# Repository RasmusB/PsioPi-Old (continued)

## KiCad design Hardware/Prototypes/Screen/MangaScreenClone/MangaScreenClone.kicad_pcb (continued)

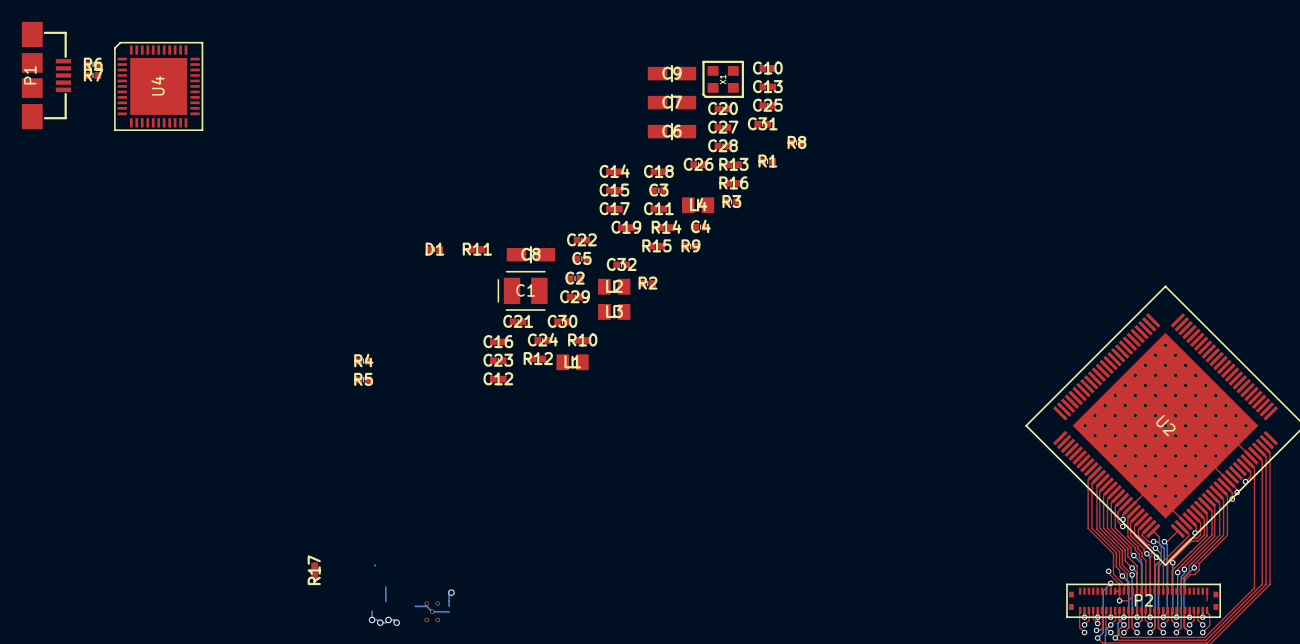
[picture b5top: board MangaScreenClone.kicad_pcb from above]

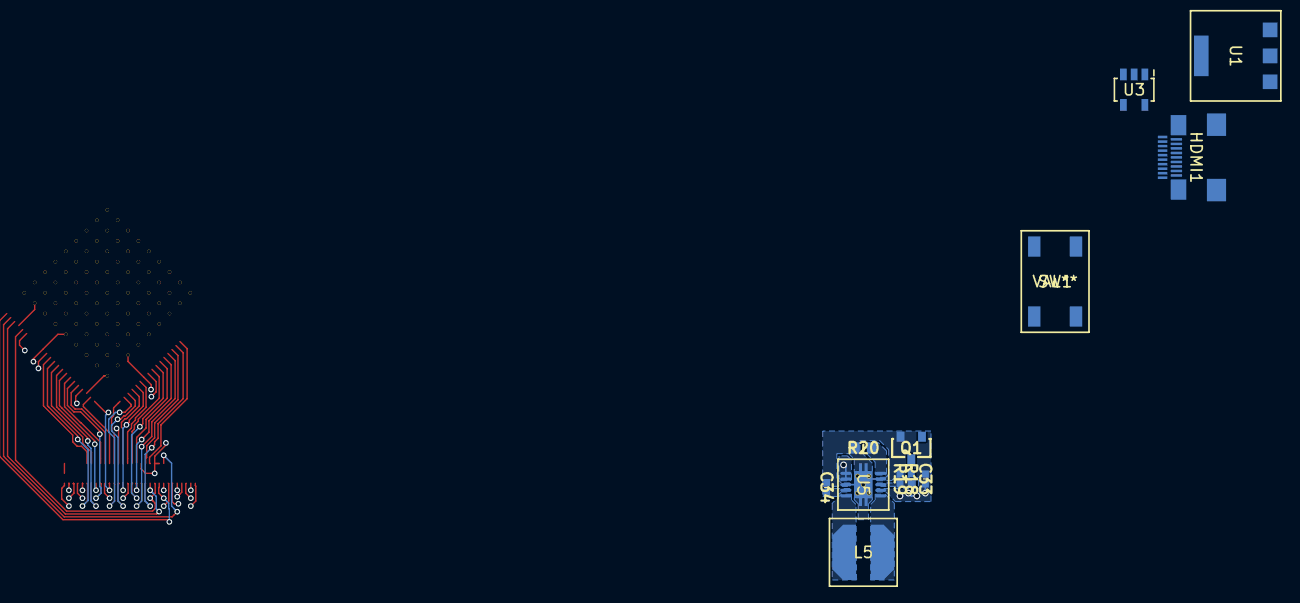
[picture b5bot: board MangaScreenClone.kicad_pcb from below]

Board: 4 copper layers, 71 parts (12 on the bottom side), 85 nets.

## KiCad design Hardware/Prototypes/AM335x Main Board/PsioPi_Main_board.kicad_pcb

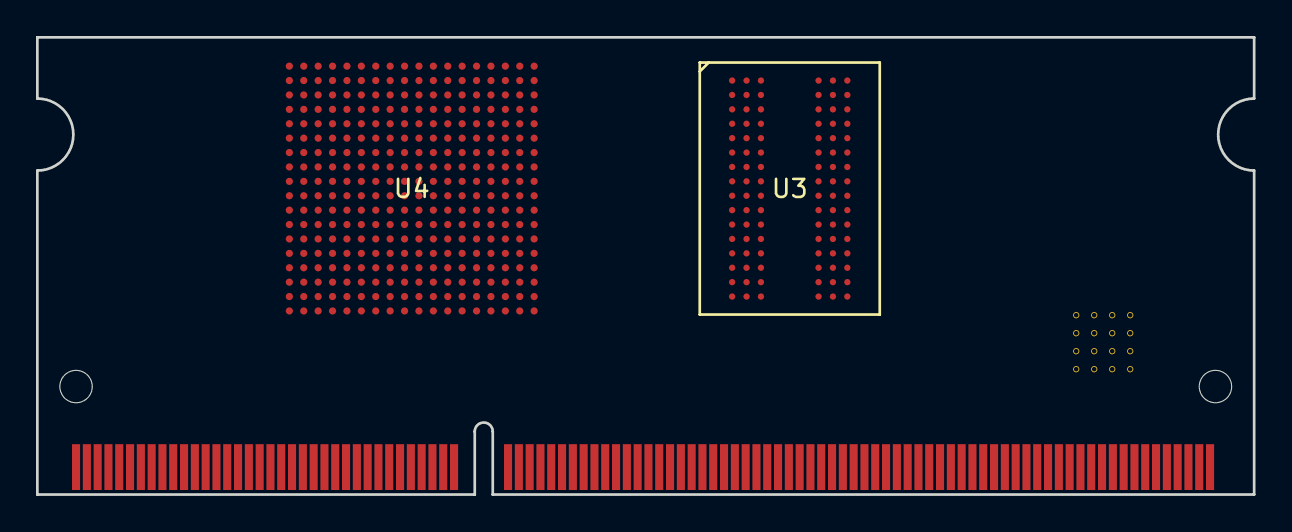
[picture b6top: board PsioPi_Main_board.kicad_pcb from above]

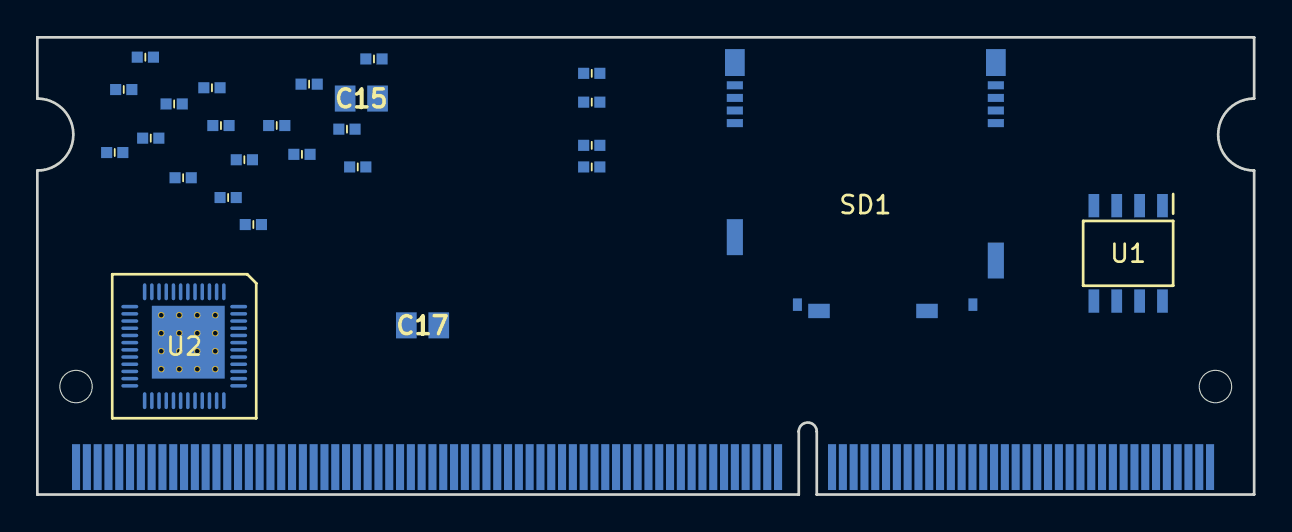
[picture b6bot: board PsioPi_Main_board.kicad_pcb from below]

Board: 2 copper layers, 67.6 x 25.4 mm, 29 parts (26 on the bottom side), 5 nets, no tracks yet.

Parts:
C1: 1n 50V; C-0402-1005
C2, C3, C4, C5, C6, C7, C8, C9, C10, C11, C12, C13, C14, C14#2, C16, C18: 0µ1 6V3; C-0402-1005
C15, C17: 10µ 10V; C-0805-2012
K1: DUMMY_KEY; SODIMM-204-For_daugher_card
R1, R2: 10k 1%; R-0402-1005
R3: 1k5 1%; R-0402-1005
R4: 240 1%; R-0402-1005
SD1: SCHA5B0200; ALPS-SCHA5B0200_MICRO-SD
U1: TL5209; SO8
U2: TPS65217C; PVQFN-48_ATMEL
U3: AS4C256M16D3L-12BCN; FBGA-96_DDR3
U4: AM3358BZCZ100; PBGA-N324_TI-ZCZ

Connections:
/DDR3 Memory/DDR_RESET: R3.2, U3.T2
DDR_VREF: C1.1, C2.1, R1.1, R2.1, U3.H1, U3.M8
GNDD: C1.2, C2.2, C3.2, C4.2, C5.2, C6.2, C7.2, C8.2, C9.2, C10.2, C11.2, C12.2, C13.2, C14.2, C14#2.2, C15.2, C16.2, C17.2, C18.2, R2.2, R4.1, U3.A9, U3.B1, U3.B3, U3.B9, U3.D1, U3.D8, U3.E1, U3.E2, U3.E8, U3.F9, U3.G1, U3.G8, U3.G9, U3.J2, U3.J8, U3.M1, U3.M9, U3.P1, U3.P9, U3.T1, U3.T9
unnamed: R4.2, U3.L8
VDDS_DDR: C3.1, C4.1, C5.1, C6.1, C7.1, C8.1, C9.1, C10.1, C11.1, C12.1, C13.1, C14.1, C14#2.1, C15.1, C16.1, C17.1, C18.1, R1.2, R3.1, U3.A1, U3.A8, U3.B2, U3.C1, U3.C9, U3.D2, U3.D9, U3.E9, U3.F1, U3.G7, U3.H2, U3.H9, U3.K2, U3.K8, U3.N1, U3.N9, U3.R1, U3.R9

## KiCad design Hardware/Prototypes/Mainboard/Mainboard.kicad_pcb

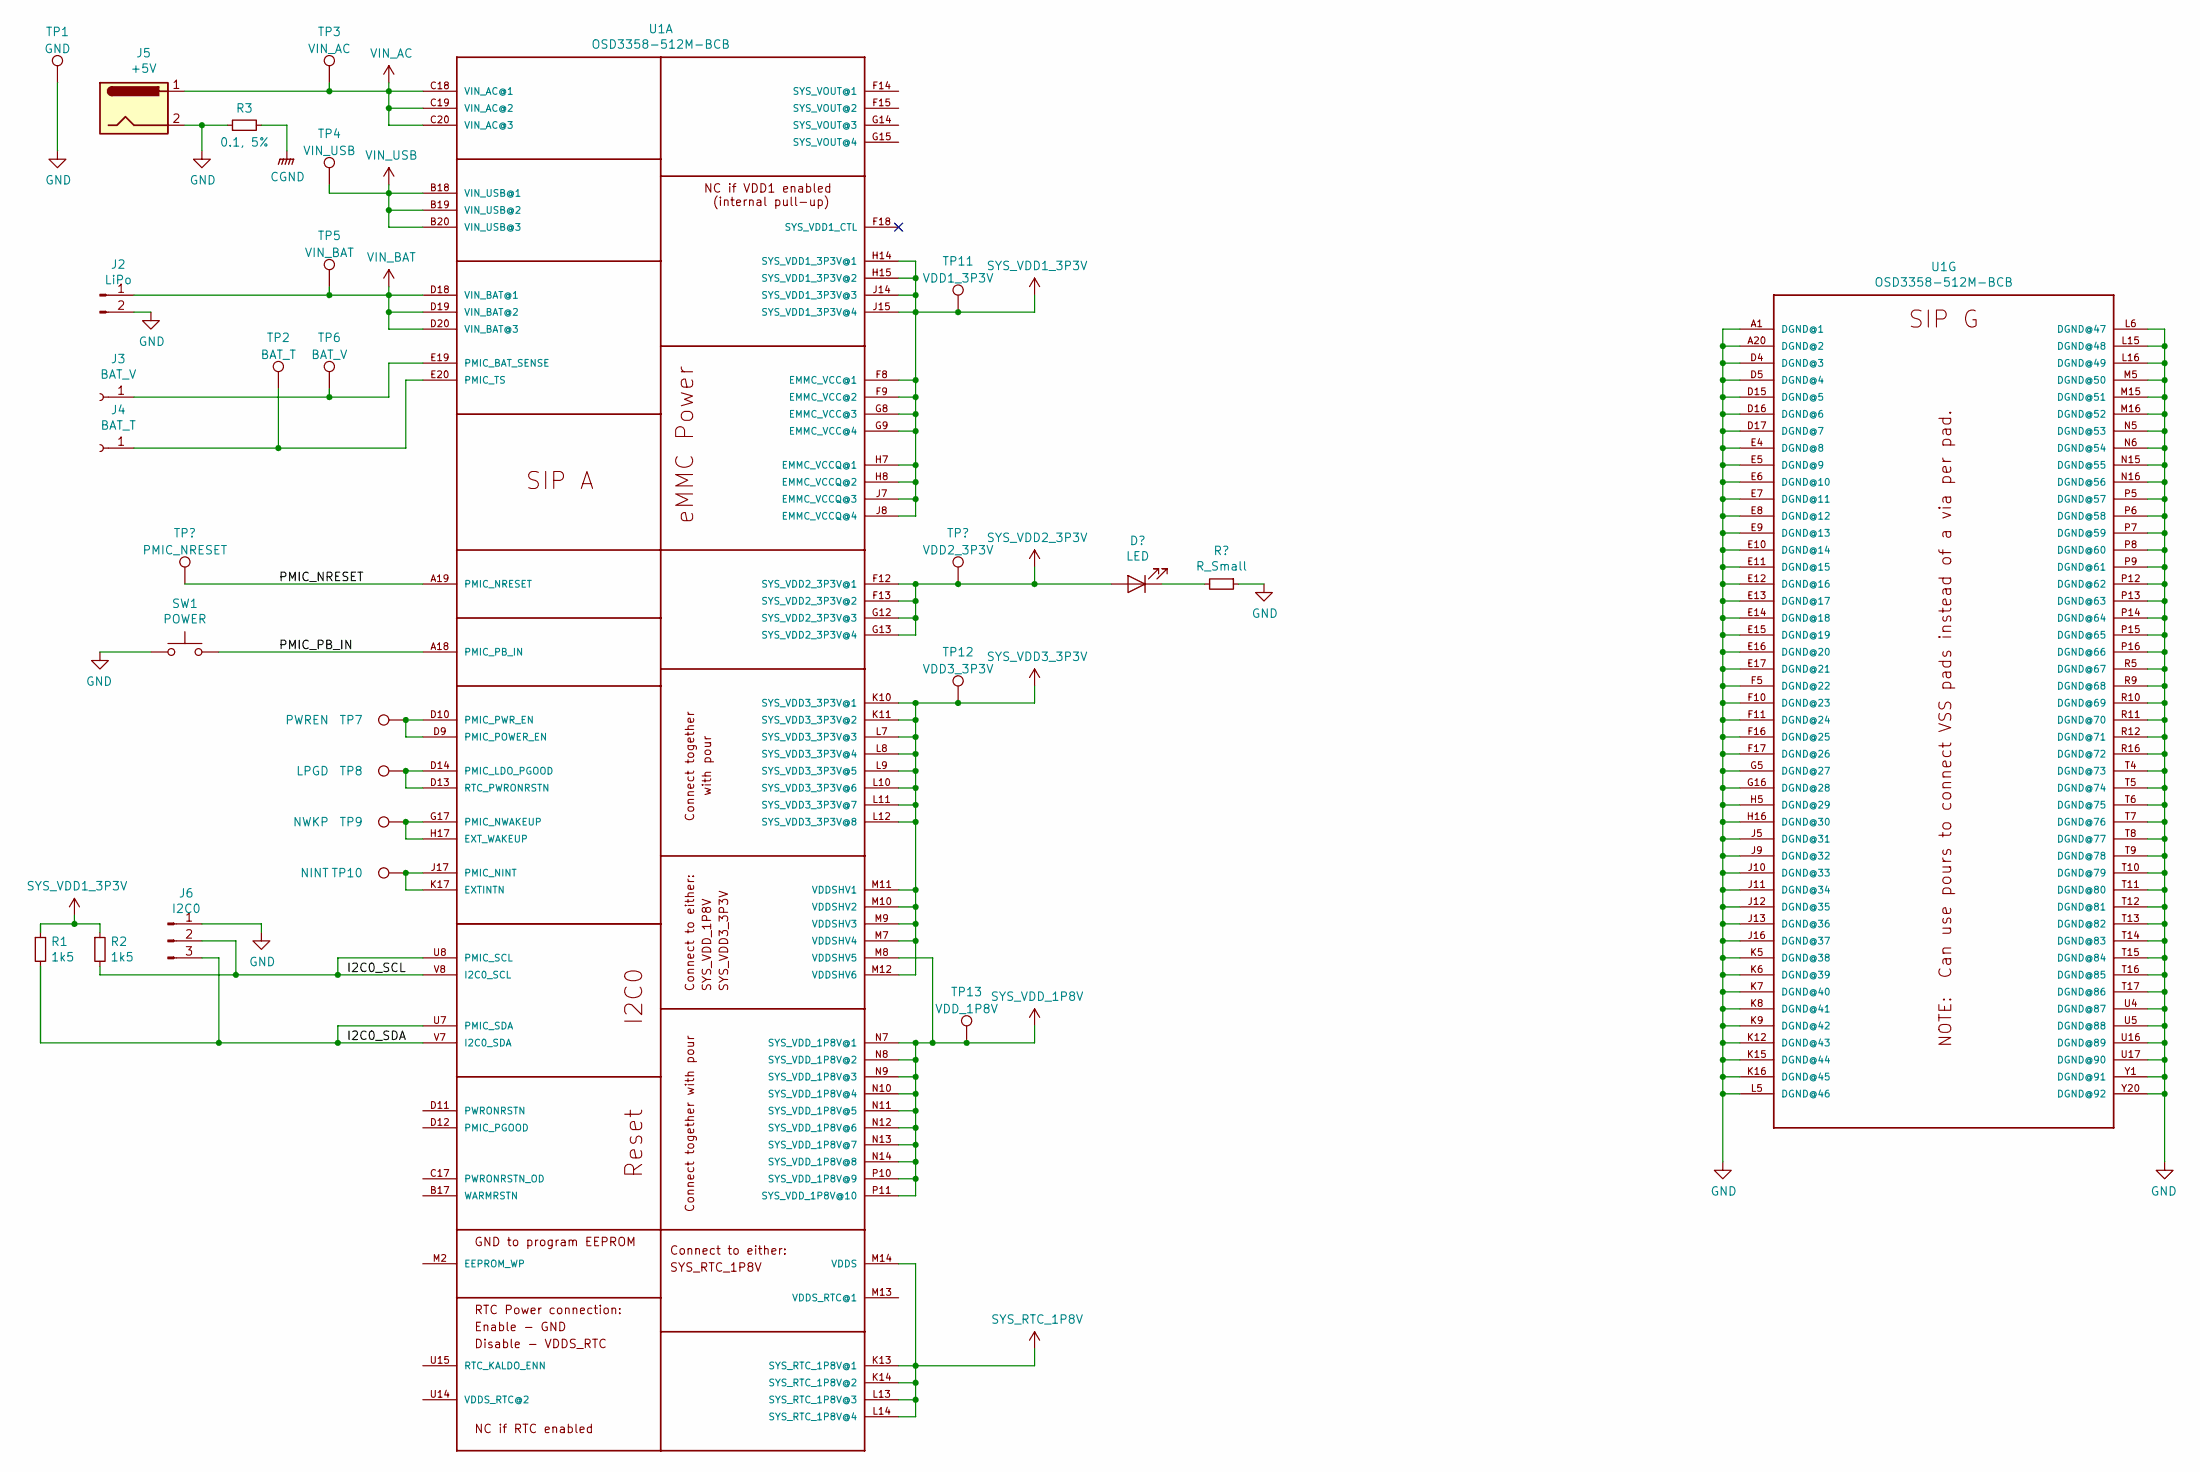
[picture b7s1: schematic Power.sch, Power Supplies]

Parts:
J2: LiPo; JST_PH_B2B-PH-K_1x02_P2.00mm_Vertical
J3: BAT_V; TestPoint_THTPad_D1.5mm_Drill0.7mm
J4: BAT_T; TestPoint_THTPad_D1.5mm_Drill0.7mm
J5: +5V; BarrelJack_Wuerth_6941xx301002
J6: I2C0; PinHeader_1x03_P2.54mm_Vertical
R1, R2: 1k5; R_0603_1608Metric
R3: 0.1, 5%; R_0603_1608Metric_Pad1.05x0.95mm_HandSolder
SW1: POWER; SW_SPST_B3SL-1002P
TP1: GND; TestPoint_Keystone_5015_Micro-Minature
TP2: BAT_T; TestPoint_Pad_D1.0mm
TP3: VIN_AC; TestPoint_Pad_D1.0mm
TP4: VIN_USB; TestPoint_Pad_D1.0mm
TP5: VIN_BAT; TestPoint_Pad_D1.0mm
TP6: BAT_V; TestPoint_Pad_D1.0mm
TP7: PWREN; TestPoint_Pad_D1.0mm
TP8: LPGD; TestPoint_Pad_D1.0mm
TP9: NWKP; TestPoint_Pad_D1.0mm
TP10: NINT; TestPoint_Pad_D1.0mm
TP11: VDD1_3P3V; TestPoint_Pad_D1.0mm
TP12: VDD3_3P3V; TestPoint_Pad_D1.0mm
TP13: VDD_1P8V; TestPoint_Pad_D1.0mm
U1: OSD3358-512M-BCB; OSD335X-BGA-400

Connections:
/Power/I2C0_SCL: J6.2, R2.2, U1.U8 (PMIC_SCL), U1.V8 (I2C0_SCL)
/Power/I2C0_SDA: J6.3, R1.2, U1.U7 (PMIC_SDA), U1.V7 (I2C0_SDA)
/Power/PMIC_NRESET: U1.A19 (PMIC_NRESET); also elsewhere on the board
/Power/PMIC_PB_IN: SW1.2, U1.A18 (PMIC_PB_IN)
CGND: R3.2; also elsewhere on the board
GND: J2.2, J5.2, J6.1, R3.1, SW1.1, TP1.1, U1.A1 (DGND@1), U1.A20 (DGND@2), U1.D4 (DGND@3), U1.D5 (DGND@4), U1.D15 (DGND@5), U1.D16 (DGND@6), U1.D17 (DGND@7), U1.E4 (DGND@8), U1.E5 (DGND@9), U1.E6 (DGND@10), U1.E7 (DGND@11), U1.E8 (DGND@12), U1.E9 (DGND@13), U1.E10 (DGND@14), U1.E11 (DGND@15), U1.E12 (DGND@16), U1.E13 (DGND@17), U1.E14 (DGND@18), U1.E15 (DGND@19), U1.E16 (DGND@20), U1.E17 (DGND@21), U1.F5 (DGND@22), U1.F10 (DGND@23), U1.F11 (DGND@24), U1.F16 (DGND@25), U1.F17 (DGND@26), U1.G5 (DGND@27), U1.G16 (DGND@28), U1.H5 (DGND@29), U1.H16 (DGND@30), U1.J5 (DGND@31), U1.J9 (DGND@32), U1.J10 (DGND@33), U1.J11 (DGND@34), U1.J12 (DGND@35), U1.J13 (DGND@36), U1.J16 (DGND@37), U1.K5 (DGND@38), U1.K6 (DGND@39), U1.K7 (DGND@40), U1.K8 (DGND@41), U1.K9 (DGND@42), U1.K12 (DGND@43), U1.K15 (DGND@44), U1.K16 (DGND@45), U1.L5 (DGND@46), U1.L6 (DGND@47), U1.L15 (DGND@48), U1.L16 (DGND@49), U1.M5 (DGND@50), U1.M15 (DGND@51), U1.M16 (DGND@52), U1.N5 (DGND@53), U1.N6 (DGND@54), U1.N15 (DGND@55), U1.N16 (DGND@56), U1.P5 (DGND@57), U1.P6 (DGND@58), U1.P7 (DGND@59), U1.P8 (DGND@60), U1.P9 (DGND@61), U1.P12 (DGND@62), U1.P13 (DGND@63), U1.P14 (DGND@64), U1.P15 (DGND@65), U1.P16 (DGND@66), U1.R5 (DGND@67), U1.R9 (DGND@68), U1.R10 (DGND@69), U1.R11 (DGND@70), U1.R12 (DGND@71), U1.R16 (DGND@72), U1.T4 (DGND@73), U1.T5 (DGND@74), U1.T6 (DGND@75), U1.T7 (DGND@76), U1.T8 (DGND@77), U1.T9 (DGND@78), U1.T10 (DGND@79), U1.T11 (DGND@80), U1.T12 (DGND@81), U1.T13 (DGND@82), U1.T14 (DGND@83), U1.T15 (DGND@84), U1.T16 (DGND@85), U1.T17 (DGND@86), U1.U4 (DGND@87), U1.U5 (DGND@88), U1.U16 (DGND@89), U1.U17 (DGND@90), U1.Y1 (DGND@91), U1.Y20 (DGND@92); also elsewhere on the board
unnamed: J3.1, TP6.1, U1.E19 (PMIC_BAT_SENSE)
unnamed: J4.1, TP2.1, U1.E20 (PMIC_TS)
unnamed: TP7.1, U1.D9 (PMIC_POWER_EN), U1.D10 (PMIC_PWR_EN)
unnamed: TP8.1, U1.D13 (RTC_PWRONRSTN), U1.D14 (PMIC_LDO_PGOOD)
unnamed: TP9.1, U1.G17 (PMIC_NWAKEUP), U1.H17 (EXT_WAKEUP)
unnamed: TP10.1, U1.J17 (PMIC_NINT), U1.K17 (EXTINTN)
SYS_RTC_1P8V: U1.K13 (SYS_RTC_1P8V@1), U1.K14 (SYS_RTC_1P8V@2), U1.L13 (SYS_RTC_1P8V@3), U1.L14 (SYS_RTC_1P8V@4), U1.M14 (VDDS)
SYS_VDD1_3P3V: R1.1, R2.1, TP11.1, U1.F8 (EMMC_VCC@1), U1.F9 (EMMC_VCC@2), U1.G8 (EMMC_VCC@3), U1.G9 (EMMC_VCC@4), U1.H7 (EMMC_VCCQ@1), U1.H8 (EMMC_VCCQ@2), U1.H14 (SYS_VDD1_3P3V@1), U1.H15 (SYS_VDD1_3P3V@2), U1.J7 (EMMC_VCCQ@3), U1.J8 (EMMC_VCCQ@4), U1.J14 (SYS_VDD1_3P3V@3), U1.J15 (SYS_VDD1_3P3V@4)
SYS_VDD3_3P3V: TP12.1, U1.K10 (SYS_VDD3_3P3V@1), U1.K11 (SYS_VDD3_3P3V@2), U1.L7 (SYS_VDD3_3P3V@3), U1.L8 (SYS_VDD3_3P3V@4), U1.L9 (SYS_VDD3_3P3V@5), U1.L10 (SYS_VDD3_3P3V@6), U1.L11 (SYS_VDD3_3P3V@7), U1.L12 (SYS_VDD3_3P3V@8), U1.M7 (VDDSHV4), U1.M9 (VDDSHV3), U1.M10 (VDDSHV2), U1.M11 (VDDSHV1), U1.M12 (VDDSHV6)
SYS_VDD_1P8V: TP13.1, U1.M8 (VDDSHV5), U1.N7 (SYS_VDD_1P8V@1), U1.N8 (SYS_VDD_1P8V@2), U1.N9 (SYS_VDD_1P8V@3), U1.N10 (SYS_VDD_1P8V@4), U1.N11 (SYS_VDD_1P8V@5), U1.N12 (SYS_VDD_1P8V@6), U1.N13 (SYS_VDD_1P8V@7), U1.N14 (SYS_VDD_1P8V@8), U1.P10 (SYS_VDD_1P8V@9), U1.P11 (SYS_VDD_1P8V@10)
VIN_AC: J5.1, TP3.1, U1.C18 (VIN_AC@1), U1.C19 (VIN_AC@2), U1.C20 (VIN_AC@3)
VIN_BAT: J2.1, TP5.1, U1.D18 (VIN_BAT@1), U1.D19 (VIN_BAT@2), U1.D20 (VIN_BAT@3)
VIN_USB: TP4.1, U1.B18 (VIN_USB@1), U1.B19 (VIN_USB@2), U1.B20 (VIN_USB@3); also elsewhere on the board

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
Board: 4 copper layers, 25 parts (0 on the bottom side), 19 nets, no tracks yet.

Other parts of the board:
J1: USB_B_Micro; USB_Micro-B_Molex_47346-0001
JP1: PMIC_NRESET; PinHeader_1x02_P2.54mm_Vertical

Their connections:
/Power/PMIC_NRESET: JP1.2; also elsewhere on the board
CGND: J1.6; also elsewhere on the board
GND: J1.5, JP1.1; also elsewhere on the board
VIN_USB: J1.1; also elsewhere on the board

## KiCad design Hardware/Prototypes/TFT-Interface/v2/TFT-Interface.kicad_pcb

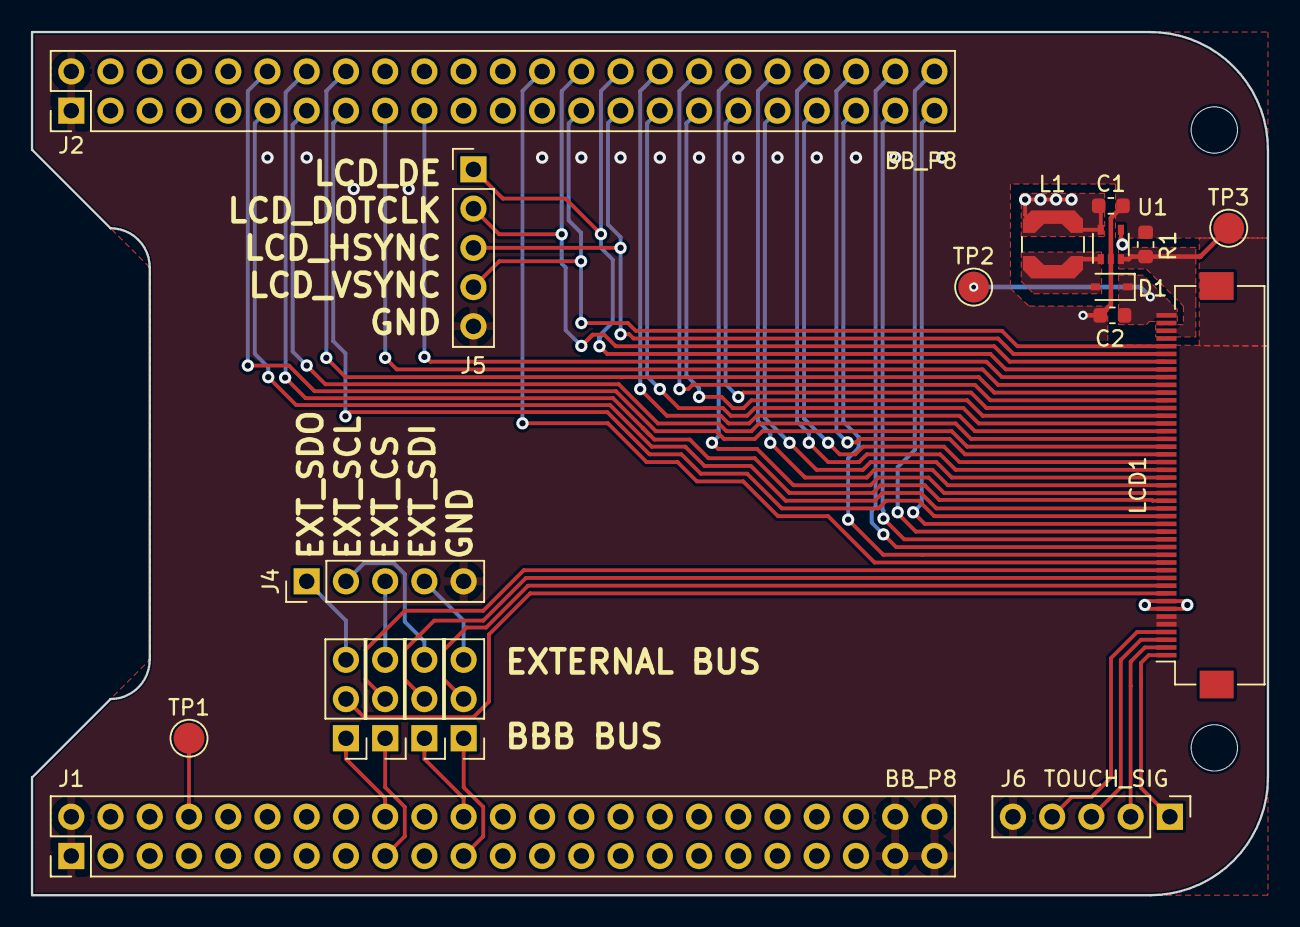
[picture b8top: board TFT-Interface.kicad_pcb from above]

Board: 4 copper layers, 80.0 x 55.9 mm, 19 parts (0 on the bottom side), 52 nets.

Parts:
C1: 4µ7 10v; C_0603_1608Metric
C2: 1µ 50v; C_0603_1608Metric
D1: NSR0240HT1G; D_SOD-323
J1, J2: BB_P8; PinHeader_2x23_P2.54mm_Vertical
J4: EXT_SPI; PinHeader_1x05_P2.54mm_Vertical
J5: LCD_CONTROL; PinHeader_1x05_P2.54mm_Vertical
J6: TOUCH_SIG; PinHeader_1x05_P2.54mm_Vertical
JUMPER1: SDO; PinHeader_1x03_P2.54mm_Vertical
JUMPER2: SCL; PinHeader_1x03_P2.54mm_Vertical
JUMPER3: CS; PinHeader_1x03_P2.54mm_Vertical
JUMPER4: SDI; PinHeader_1x03_P2.54mm_Vertical
L1: LPS4018-103MRB; L_Coilcraft_LPS4018
LCD1: E50RG84885LWAM520-CA; Hirose_FH12-45S-0.5SH_1x45-1MP_P0.50mm_Horizontal
R1: 5R1; R_0603_1608Metric
TP1: +5VP; TestPoint_Pad_D2.0mm
TP2: LED+; TestPoint_Pad_D2.0mm
TP3: LED-; TestPoint_Pad_D2.0mm
U1: TPS61169; SOT-353_SC-70-5

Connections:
+3V3: J1.3, J1.4, LCD1.7, LCD1.8
+5V: J1.5, J1.6
+5VP: C1.1, J1.7, J1.8, L1.2, TP1.1, U1.5
/BBB_CS: J1.17, JUMPER3.1
/BBB_SCL: J1.22, JUMPER2.1
/BBB_SDI: J1.21, JUMPER4.1
/BBB_SDO: J1.18, JUMPER1.1
/EXT_CS: J4.3, JUMPER3.3
/EXT_SCL: J4.2, JUMPER2.3
/EXT_SDI: J4.4, JUMPER4.3
/EXT_SDO: J4.1, JUMPER1.3
/LCD_B0: J2.19, LCD1.37
/LCD_B1: J2.17, LCD1.36
/LCD_B2: J2.16, LCD1.35
/LCD_B3: J2.34, LCD1.34
/LCD_B4: J2.35, LCD1.33
/LCD_B5: J2.33, LCD1.32
/LCD_B6: J2.31, LCD1.31
/LCD_B7: J2.32, LCD1.30
/LCD_CS: JUMPER3.2, LCD1.12
/LCD_DE: J2.30, J5.1, LCD1.38
/LCD_DOTCLK: J2.28, J5.2, LCD1.39
/LCD_G0: J2.13, LCD1.29
/LCD_G1: J2.12, LCD1.28
/LCD_G2: J2.42, LCD1.27
/LCD_G3: J2.39, LCD1.26
/LCD_G4: J2.40, LCD1.25
/LCD_G5: J2.37, LCD1.24
/LCD_G6: J2.38, LCD1.23
/LCD_G7: J2.36, LCD1.22
/LCD_HSYNC: J2.29, J5.3, LCD1.40
/LCD_R0: J2.14, LCD1.21
/LCD_R1: J2.11, LCD1.20
/LCD_R2: J2.15, LCD1.19
/LCD_R3: J2.45, LCD1.18
/LCD_R4: J2.46, LCD1.17
/LCD_R5: J2.43, LCD1.16
/LCD_R6: J2.44, LCD1.15
/LCD_R7: J2.41, LCD1.14
/LCD_RESET: J2.26, LCD1.13
/LCD_SCL: JUMPER2.2, LCD1.11
/LCD_SDI: JUMPER4.2, LCD1.10
/LCD_SDO: JUMPER1.2, LCD1.9
/LCD_VSYNC: J2.27, J5.4, LCD1.41
/LED_SW: D1.2, L1.1, U1.1
/TOUCH_XL: J6.3, LCD1.3
/TOUCH_XR: J6.1, LCD1.1
/TOUCH_YD: J6.2, LCD1.2
/TOUCH_YU: J6.4, LCD1.4
GND: C1.2, C2.2, J1.1, J1.2, J1.43, J1.44, J1.45, J1.46, J2.1, J2.2, J4.5, J5.5, J6.5, LCD1.5, LCD1.6, R1.2, U1.2
LED+: C2.1, D1.1, LCD1.45, TP2.1
LED-: LCD1.43, R1.1, TP3.1, U1.3

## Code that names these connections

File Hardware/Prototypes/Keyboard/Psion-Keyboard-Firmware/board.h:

/*
 board.h
 
 This is how the pins are connected to the keyboard
 
 */
 
// See the keyboard schematic for row/col mapping
#define NROWS 8
#define NCOLS 12

#define ROW_01  0
#define ROW_02  4
#define ROW_03  8
#define ROW_04  7
#define ROW_05  6
#define ROW_06  3
#define ROW_07  2
#define ROW_08  1

#define COL_1   5
#define COL_2   9
#define COL_3   13
#define COL_4   12
#define COL_5   11
#define COL_6   10
#define COL_7   18
#define COL_8   19
#define COL_9   23
#define COL_10  20
#define COL_11  21
#define COL_12  22

int Rows [NROWS] = {
  ROW_01,
  ROW_02,
  ROW_03,
  ROW_04,
  ROW_05,
  ROW_06,
  ROW_07,
  ROW_08
};

int Cols [NCOLS] = {
  COL_1,
  COL_2,
  COL_3,
  COL_4,
  COL_5,
  COL_6,
  COL_7,
  COL_8,
  COL_9,
  COL_10,
  COL_11,
  COL_12
};


// New mapping for the prototype
/*
#define ROW_01  0
#define ROW_02  4
#define ROW_03  8
#define ROW_04  7
#define ROW_05  6
#define ROW_06  3
#define ROW_07  2
#define ROW_08  1

#define COL_1   5
#define COL_2   9
#define COL_3   13
#define COL_4   12
#define COL_5   11
#define COL_6   10
#define COL_7   18
#define COL_8   19
#define COL_9   23
#define COL_10  20
#define COL_11  21
#define COL_12  22
*/

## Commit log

2015-02-18 Created repo, no actual content yet
2015-02-18 Initial commit of keyboard files
2015-02-18 Added the first version of the keyboard prototype module
2015-02-18 Keymap file now supports CTRL as a modifier
2015-02-21 Started work on screen breakout board
2016-02-13 Initial work on AM335x board
2016-02-13 Some work
2016-02-13 Manga screen clone attempt
2016-02-13 More work on the keyboard
    Also an attempt to make an I2C based keyboard
2016-02-13 Initial MCAD attempt
2016-02-13 RGB screen initial commit
2016-02-13 Added sketch for scannin an unknown keyboard
2016-02-13 Inital power supply
2016-02-13 Initial branch for creating a mechanical test fit
2016-10-04 Keyboard update
    Version 1.1
2016-10-10 Reverted to 2-layer board
    Because it fits and is cheaper
2016-11-25 Further stuff done to prepare for prototypes
2019-05-27 Major data dump
2019-06-20 Moved ordered board to own folder
2019-08-16 Started work on new mainboard prototype
    Now using the new C-SIP
2019-08-16 Checkin, WIP
2019-08-19 Added PMIC_NRESET
2019-08-22 More work
    Still on the power section. Next - clamping circuit!
